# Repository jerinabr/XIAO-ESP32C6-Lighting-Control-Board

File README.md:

# Overview
This is a "generic" breakout board for the XIAO ESP32C6. Generic is in quotes because the board is primarily designed to be an addressable LED strip controller.

However, the board is designed in a way where the peripherals can be used for other purposes. This allows the same board to be used with other XIAO ESP32C6 projects.

# Features
1. Dual 3.3V -> 5V level shifter for addressable LED data
2. Onboard pullups for I2C data and clock
3. Power jumper to allow the XIAO to be powered via USB while the barrel jack is plugged in
   - This is needed since the XIAO doesn't have onboard power or-ing for the 5V input and V_USB rail
4. Connector for off-board buck converter
5. Dual connectors for UART: one for standard 2.54 mm headers and one for a 1.5 mm pitch JST connector

# Layer Stackup
This is a 2-layer board with the following stackup:

1. Signal + Power
2. Ground

This is a very simple board with relatively low speed signals so I didn't bother with a 4-layer board

# Images
## Schematic

## PCB
### Top Layer

### Bottom Layer

### Top + Bottom Layer

## 3D View

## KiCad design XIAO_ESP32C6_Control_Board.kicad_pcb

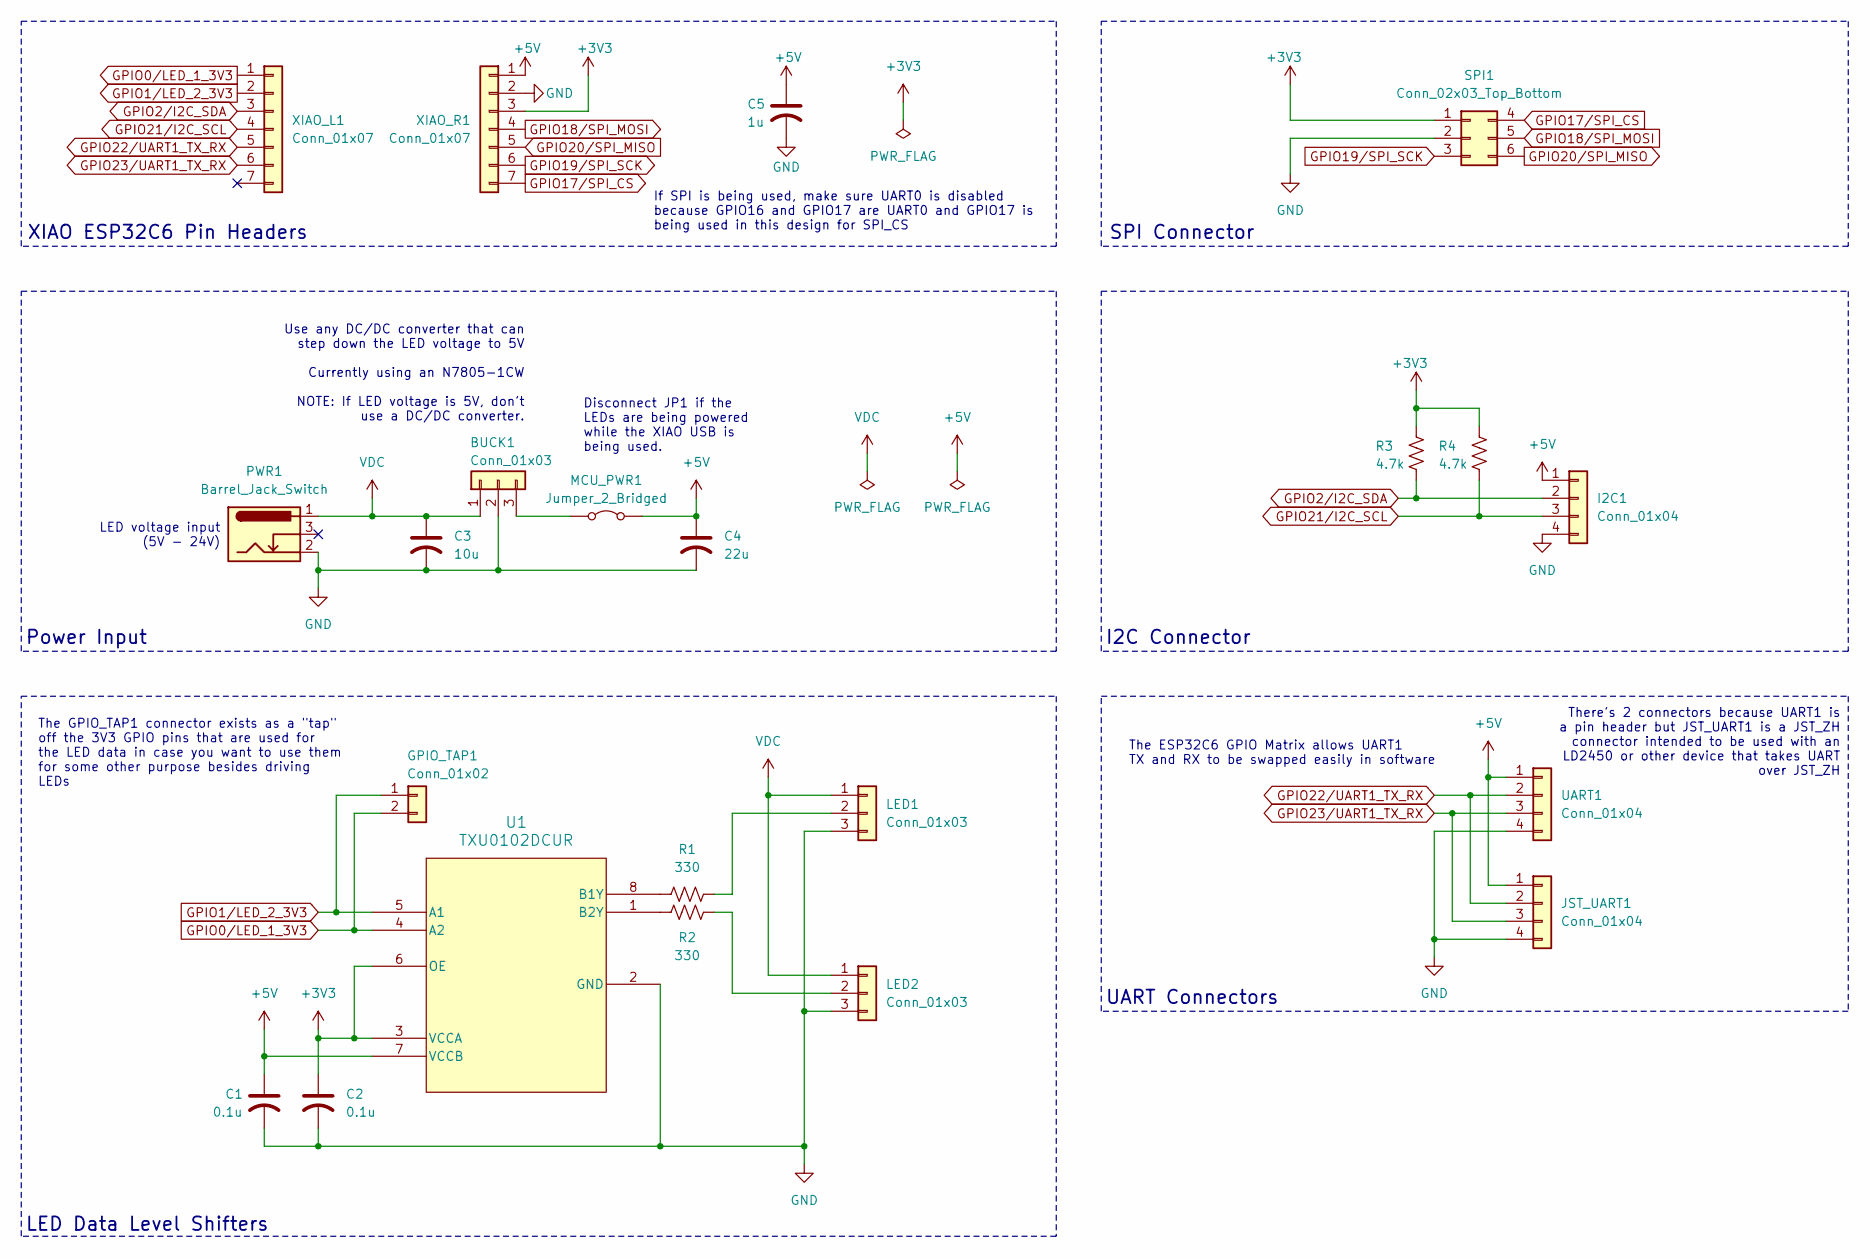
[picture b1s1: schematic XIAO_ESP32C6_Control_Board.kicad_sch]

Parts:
BUCK1: Conn_01x03; PinHeader_1x03_P2.54mm_Vertical
C1, C2: 0.1u; C_0603_1608Metric_Pad1.08x0.95mm_HandSolder
C3: 10u; C_1210_3225Metric_Pad1.33x2.70mm_HandSolder
C4: 22u; C_1210_3225Metric_Pad1.33x2.70mm_HandSolder
C5: 1u; C_0603_1608Metric_Pad1.08x0.95mm_HandSolder
GPIO_TAP1: Conn_01x02; PinHeader_1x02_P2.54mm_Vertical
I2C1: Conn_01x04; PinHeader_1x04_P2.54mm_Vertical
JST_UART1: Conn_01x04; JST_ZH_B4B-ZR_1x04_P1.50mm_Vertical
LED1, LED2: Conn_01x03; PinHeader_1x03_P2.54mm_Vertical
MCU_PWR1: Jumper_2_Bridged; PinHeader_1x02_P2.54mm_Vertical
PWR1: Barrel_Jack_Switch; CUI_PJ-002AH
R1, R2: 330; R_0603_1608Metric_Pad0.98x0.95mm_HandSolder
R3, R4: 4.7k; R_0603_1608Metric_Pad0.98x0.95mm_HandSolder
SPI1: Conn_02x03_Top_Bottom; PinHeader_2x03_P2.54mm_Vertical
U1: TXU0102DCUR; SOIC8_DCU_TEX
UART1: Conn_01x04; PinHeader_1x04_P2.54mm_Vertical
XIAO_L1: Conn_01x07; PinSocket_1x07_P2.54mm_Vertical; MPN SSK02-FPH-254-A7
XIAO_R1: Conn_01x07; PinSocket_1x07_P2.54mm_Vertical; MPN SSK02-FPH-254-A7

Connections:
+3V3: C2.1, R3.1, R4.1, SPI1.1, U1.3 (VCCA), U1.6 (OE), XIAO_R1.3
+5V: C1.1, C4.1, C5.1, I2C1.1, JST_UART1.1, MCU_PWR1.2 (B), U1.7 (VCCB), UART1.1, XIAO_R1.1
GND: BUCK1.2, C1.2, C2.2, C3.2, C4.2, C5.2, I2C1.4, JST_UART1.4, LED1.3, LED2.3, PWR1.2, SPI1.2, U1.2 (GND), UART1.4, XIAO_R1.2
GPIO0/LED_1_3V3: GPIO_TAP1.2, U1.4 (A2), XIAO_L1.1
GPIO1/LED_2_3V3: GPIO_TAP1.1, U1.5 (A1), XIAO_L1.2
GPIO2/I2C_SDA: I2C1.2, R3.2, XIAO_L1.3
GPIO17/SPI_CS: SPI1.4, XIAO_R1.7
GPIO18/SPI_MOSI: SPI1.5, XIAO_R1.4
GPIO19/SPI_SCK: SPI1.3, XIAO_R1.6
GPIO20/SPI_MISO: SPI1.6, XIAO_R1.5
GPIO21/I2C_SCL: I2C1.3, R4.2, XIAO_L1.4
GPIO22/UART1_TX_RX: JST_UART1.2, UART1.2, XIAO_L1.5
GPIO23/UART1_TX_RX: JST_UART1.3, UART1.3, XIAO_L1.6
unnamed: BUCK1.3, MCU_PWR1.1 (A)
unnamed: LED1.2, R1.2
unnamed: LED2.2, R2.1
unnamed: R1.1, U1.8 (B1Y)
unnamed: R2.2, U1.1 (B2Y)
VDC: BUCK1.1, C3.1, LED1.1, LED2.1, PWR1.1

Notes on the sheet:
There's 2 connectors because UART1 is a pin header but JST_UART1 is a JST_ZH connector intended to be used with an LD2450 or other device that takes UART over JST_ZH
LED voltage input (5V - 24V)
The GPIO_TAP1 connector exists as a "tap" off the 3V3 GPIO pins that are used for the LED data in case you want to use them for some other purpose besides driving LEDs
I2C Connector
Power Input
The ESP32C6 GPIO Matrix allows UART1 TX and RX to be swapped easily in software
SPI Connector
LED Data Level Shifters
UART Connectors
Disconnect JP1 if the LEDs are being powered while the XIAO USB is being used.
Use any DC/DC converter that can step down the LED voltage to 5V Currently using an N7805-1CW NOTE: If LED voltage is 5V, don't use a DC/DC converter.
XIAO ESP32C6 Pin Headers
If SPI is being used, make sure UART0 is disabled because GPIO16 and GPIO17 are UART0 and GPIO17 is being used in this design for SPI_CS

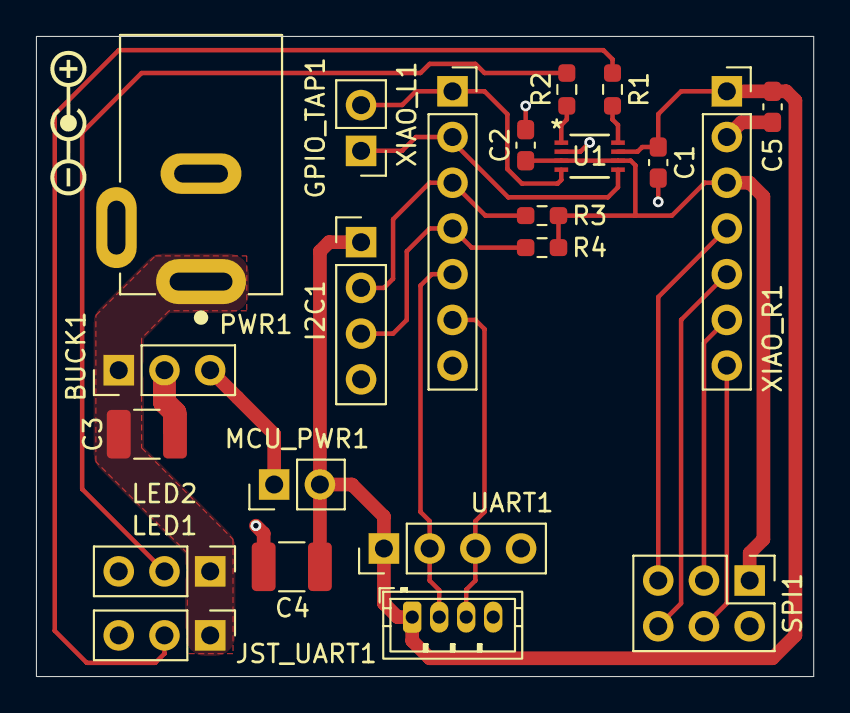
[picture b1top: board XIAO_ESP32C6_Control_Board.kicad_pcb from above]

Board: 2 copper layers, 43.2 x 35.6 mm, 22 parts (0 on the bottom side), 19 nets.
